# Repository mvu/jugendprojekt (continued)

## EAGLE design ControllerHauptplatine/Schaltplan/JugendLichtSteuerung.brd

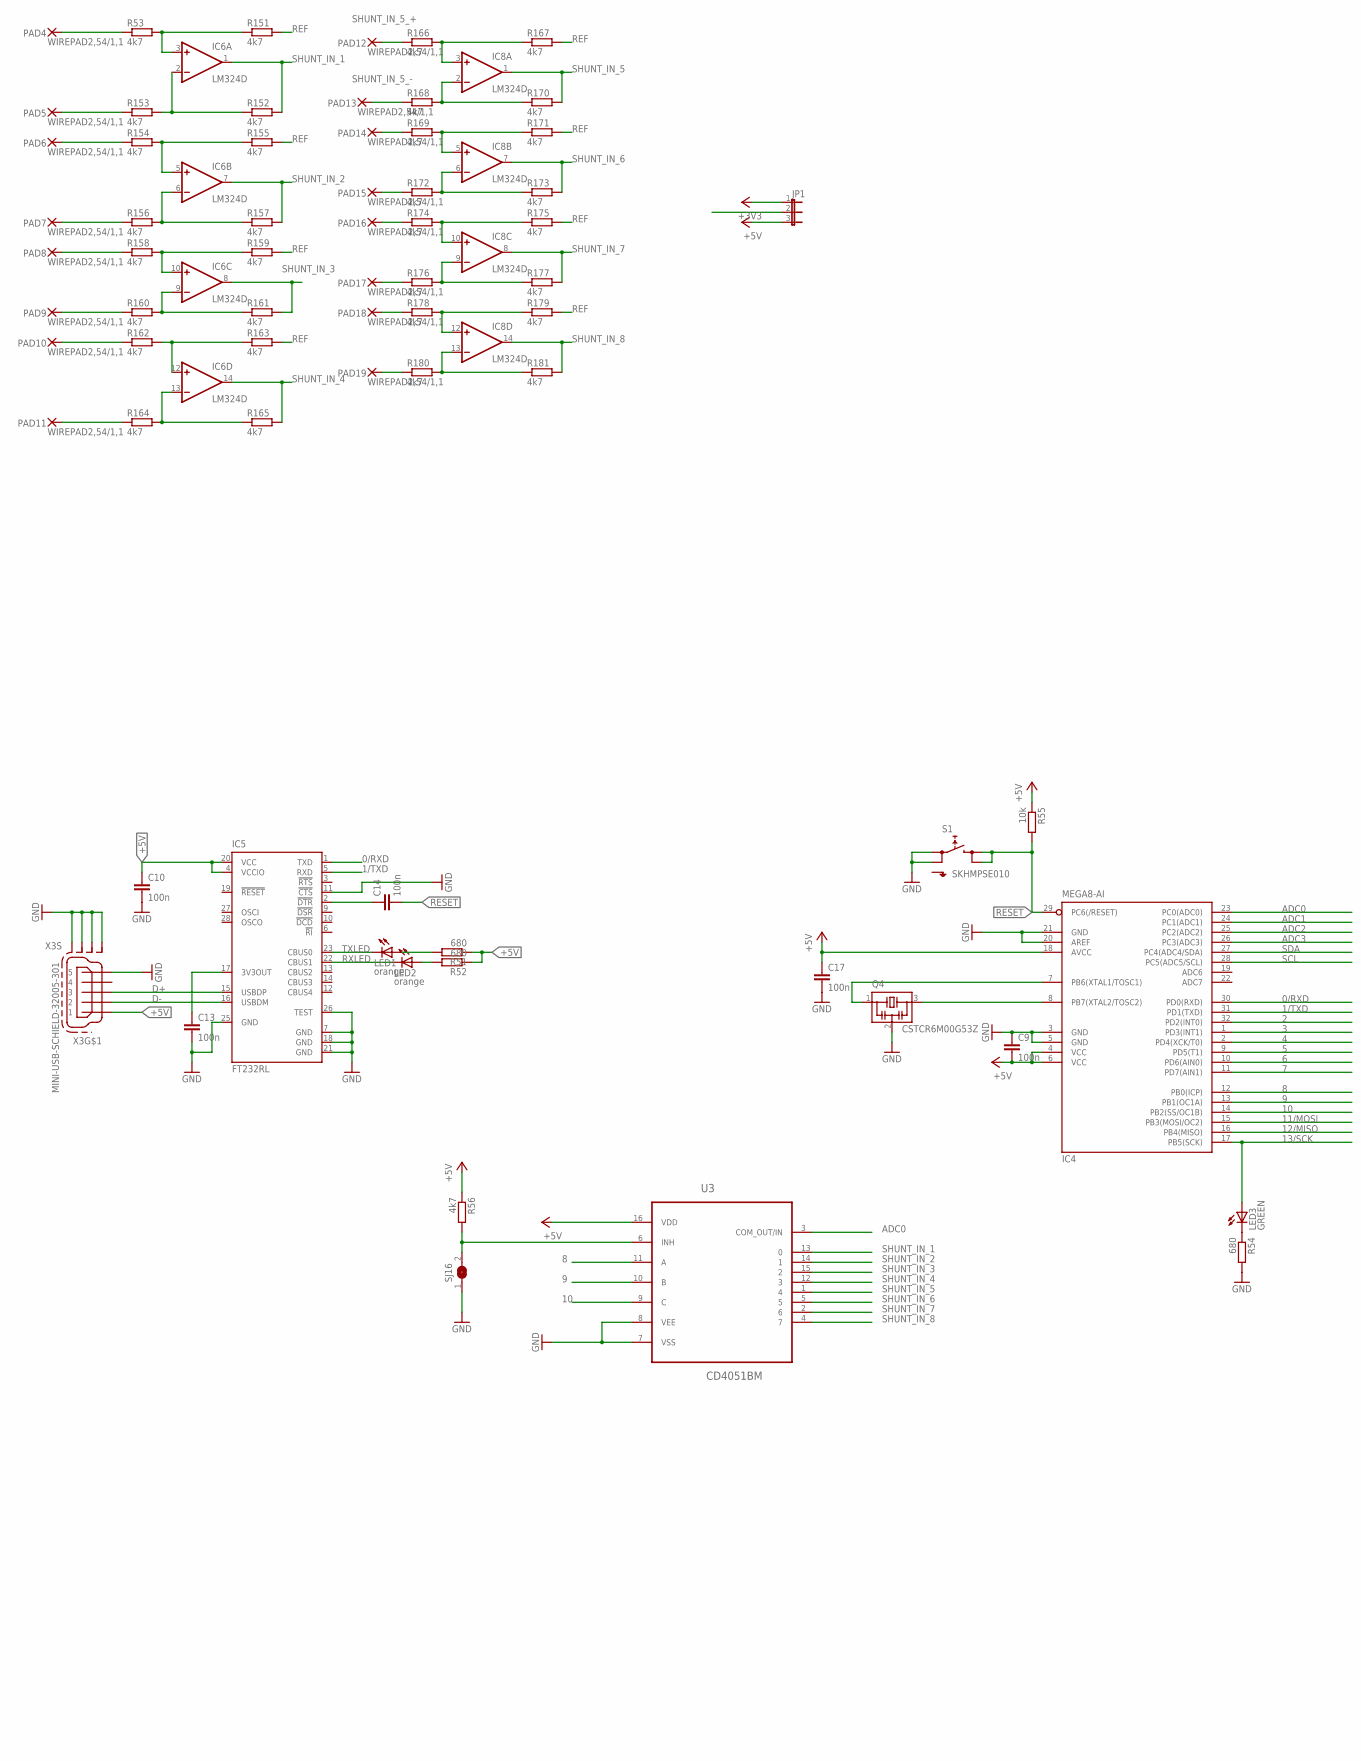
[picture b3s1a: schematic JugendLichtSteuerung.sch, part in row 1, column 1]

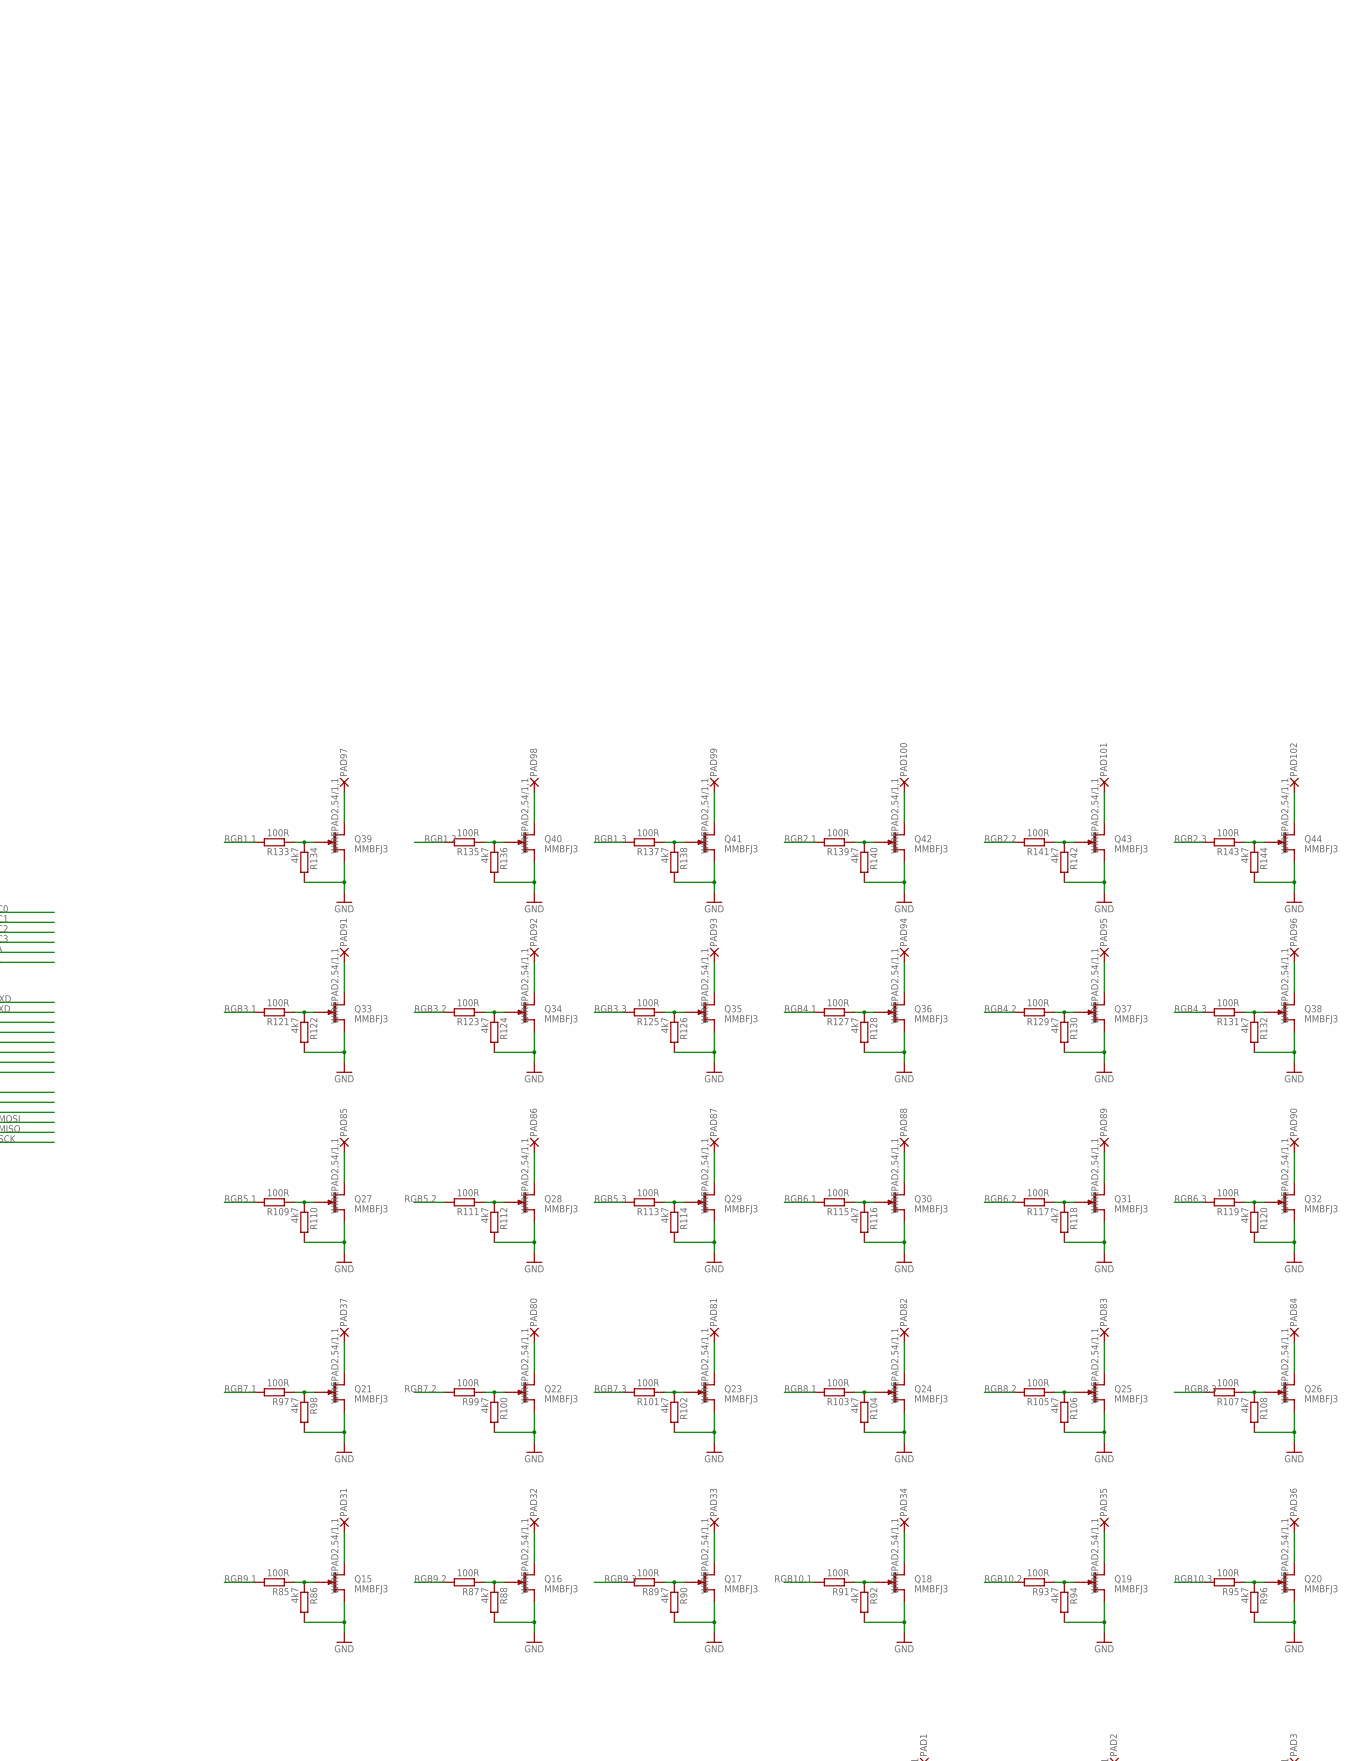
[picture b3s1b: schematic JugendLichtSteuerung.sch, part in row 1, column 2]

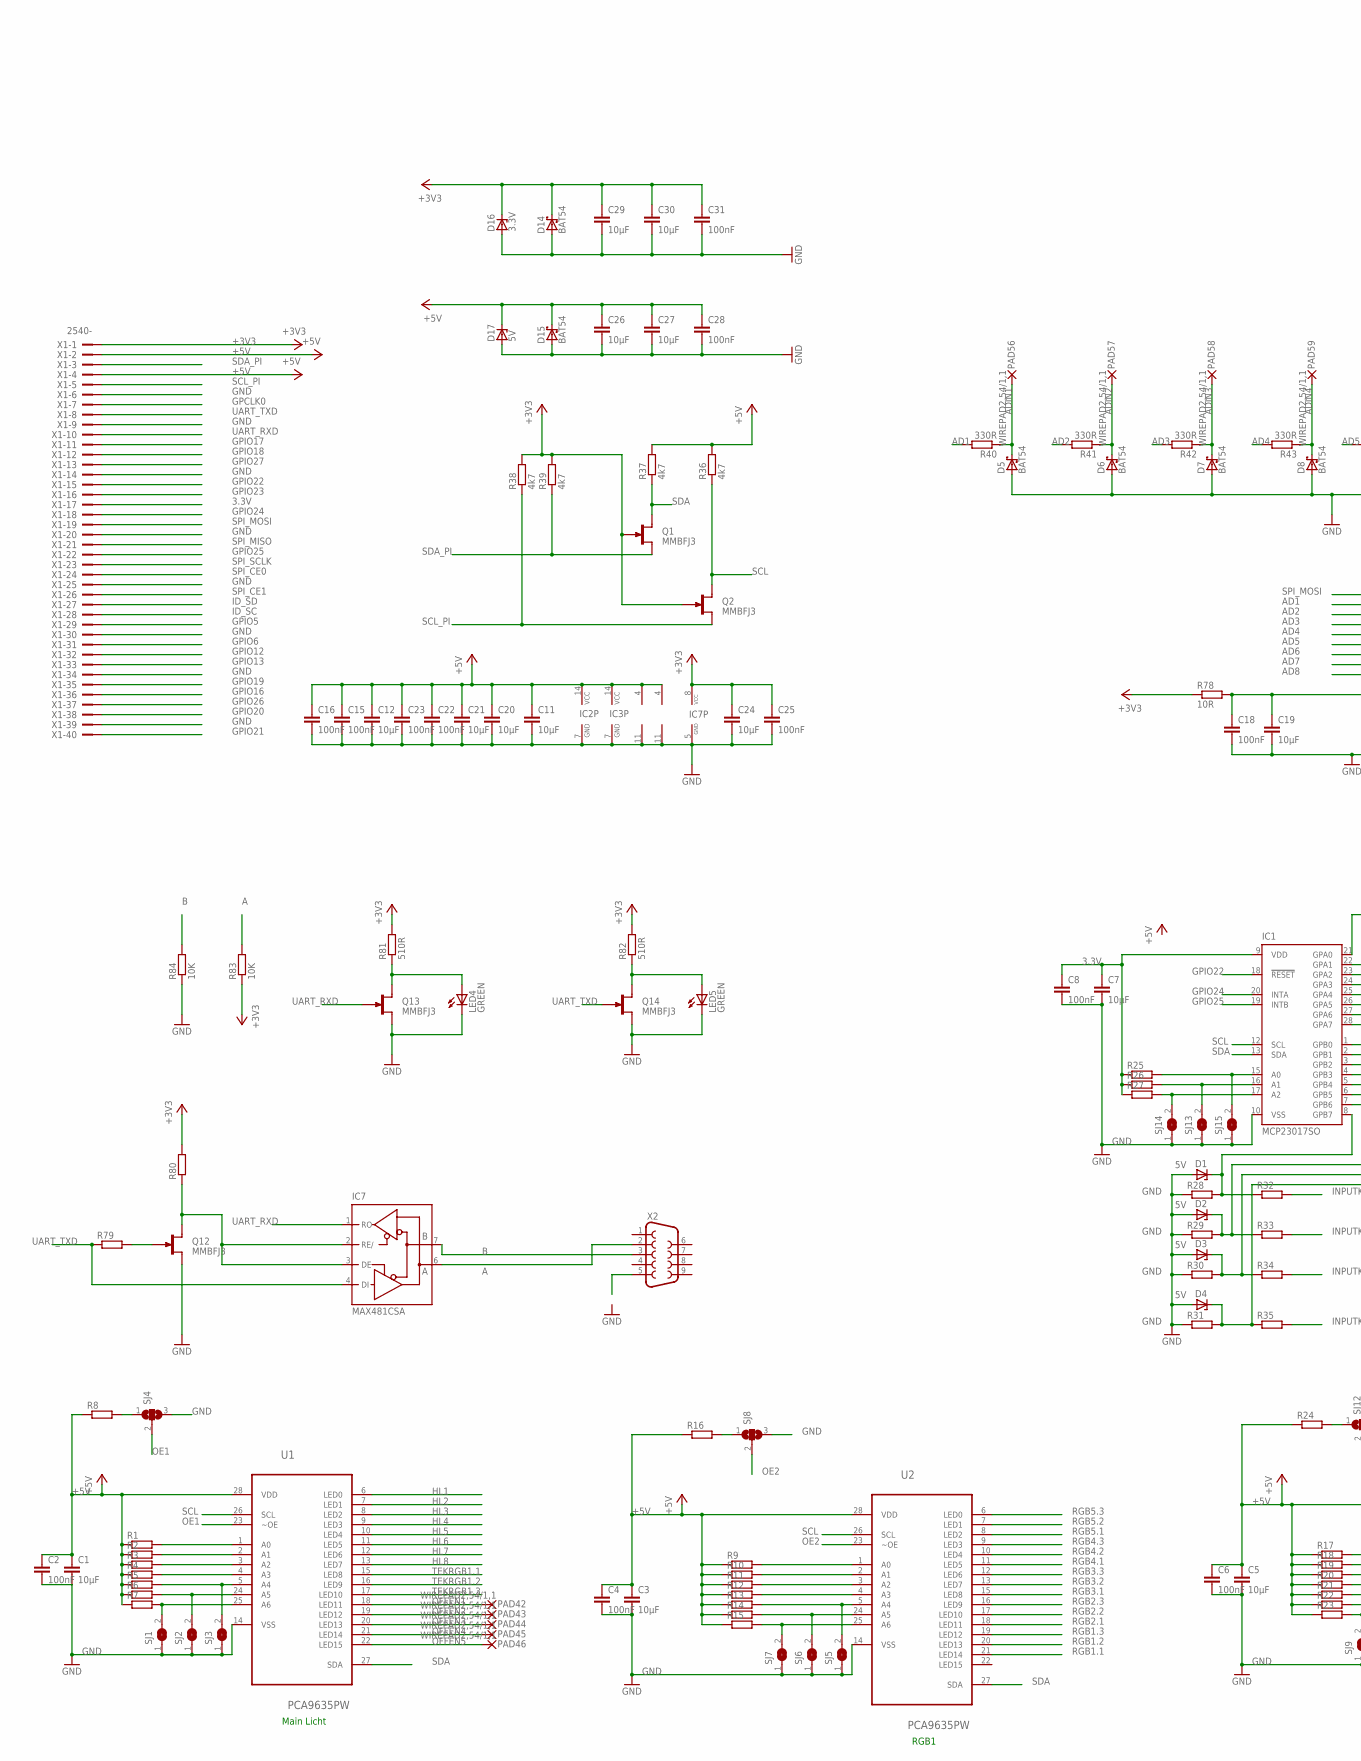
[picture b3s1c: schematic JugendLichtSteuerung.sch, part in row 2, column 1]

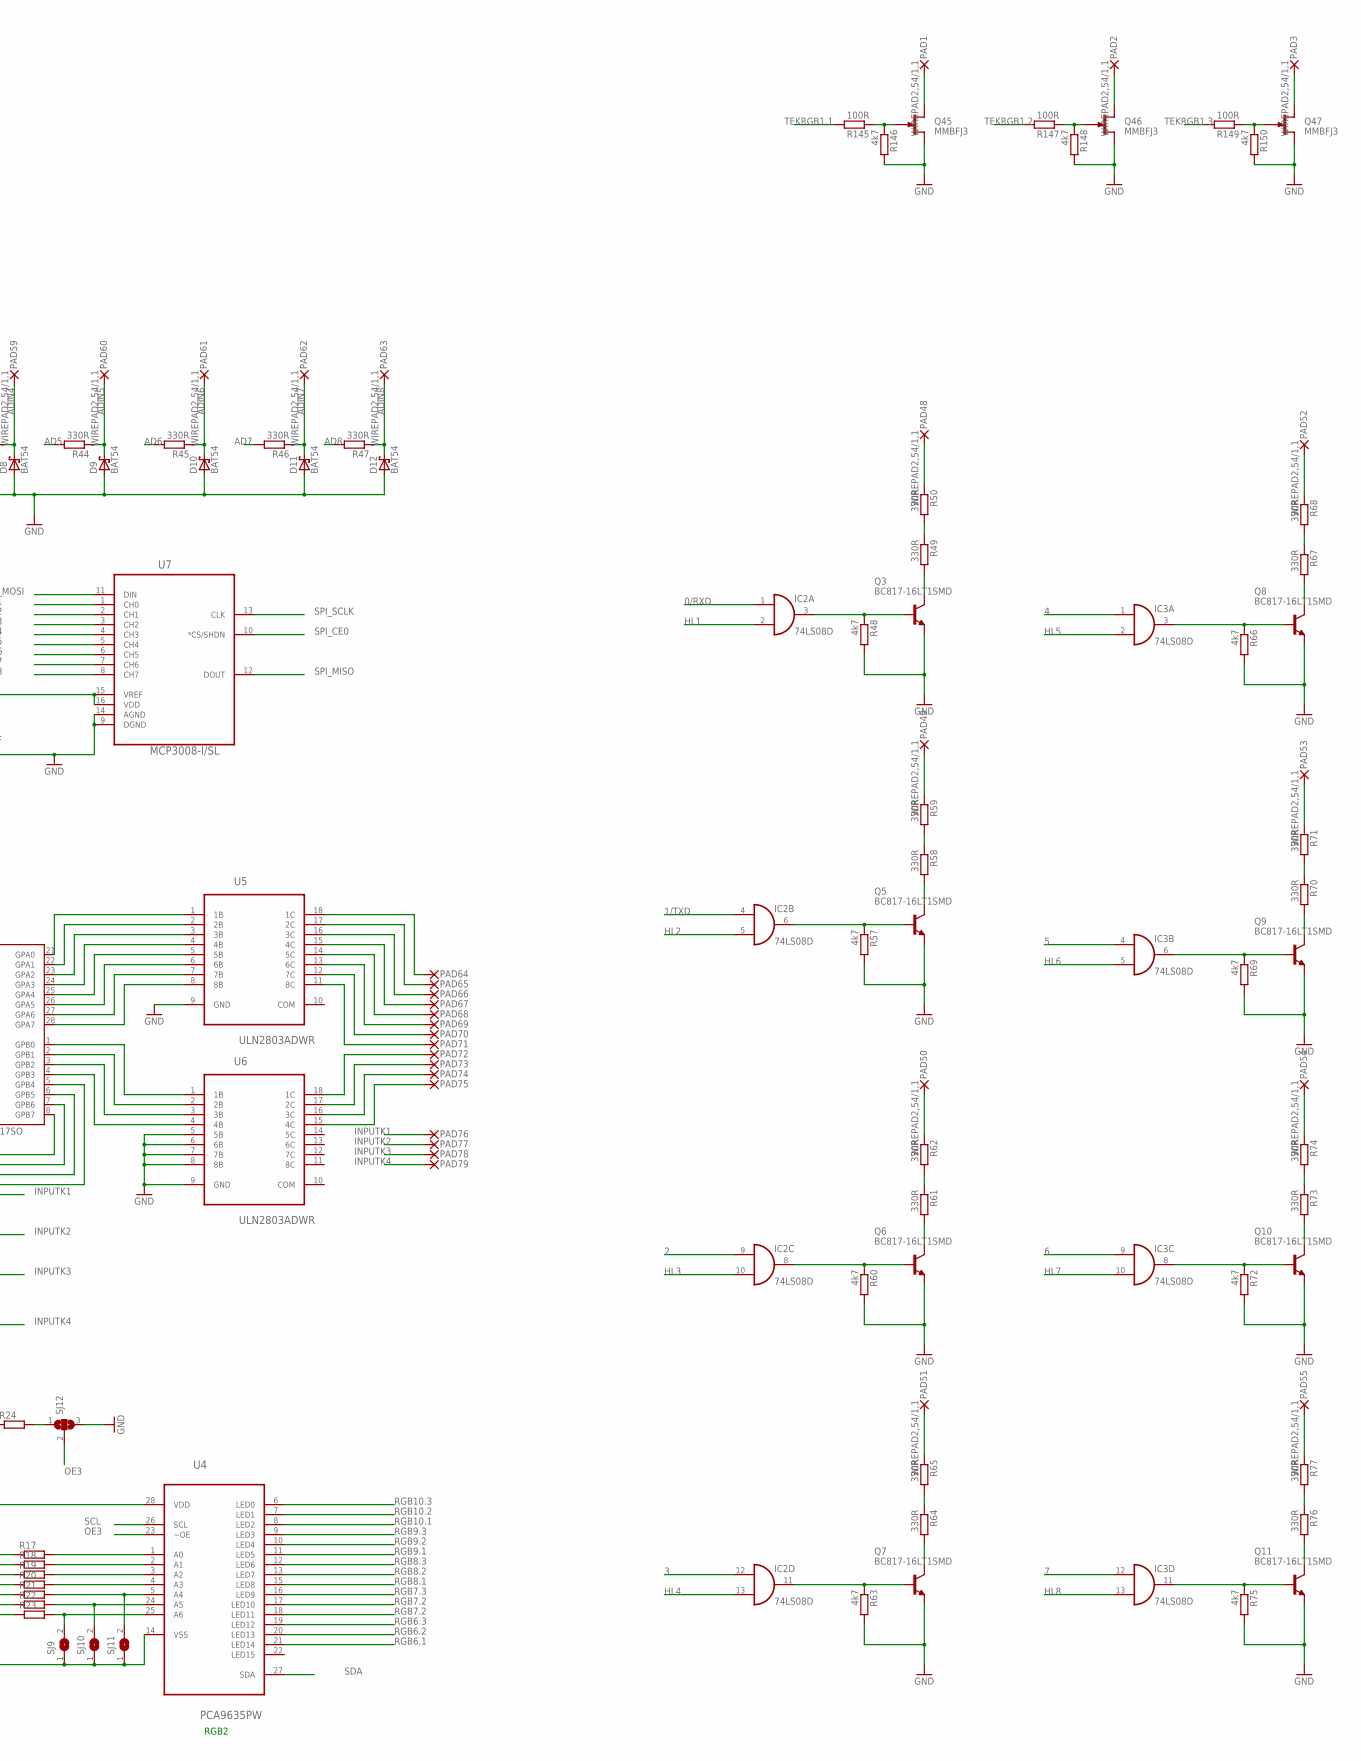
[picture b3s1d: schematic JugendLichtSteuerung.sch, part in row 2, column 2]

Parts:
C1, C3, C5, C7, C11, C12, C19, C20, C21, C24, C26, C27, C29, C30: 10µF; C0805
C2, C4, C6, C8, C15, C16, C18, C22, C23, C25, C28, C31: 100nF; C0805
C9, C10, C14: 100n; C0603
C13: 100n; C1206K
C17: 100n; C0603K
D1, D2, D3, D4, D17: 5V; SOD80C
D5, D6, D7, D8, D9, D10, D11, D12, D14, D15: BAT54; SOT23
D16: 3.3V; SOD80C
IC1: MCP23017SO; SO28W
IC2, IC3: 74LS08D; SO14
IC4: MEGA8-AI; TQFP32-08
IC5: FT232RL; SSOP28
IC6, IC8: LM324D; SO14
IC7: MAX481CSA; SO08
JP1: JP2E; JP2
LED1, LED2: orange; CHIPLED_1206
LED3, LED4, LED5: GREEN; CHIPLED_1206
PAD1, PAD2, PAD3, PAD4, PAD5, PAD6, PAD7, PAD8, PAD9, PAD10, PAD11, PAD12, PAD13, PAD14, PAD15, PAD16, PAD17, PAD18, PAD19, PAD31, PAD32, PAD33, PAD34, PAD35, PAD36, PAD37, PAD42, PAD43, PAD44, PAD45, PAD46, PAD48, PAD49, PAD50, PAD51, PAD52, PAD53, PAD54, PAD55, PAD56, PAD57, PAD58, PAD59, PAD60, PAD61, PAD62, PAD63, PAD80, PAD81, PAD82, PAD83, PAD84, PAD85, PAD86, PAD87, PAD88, PAD89, PAD90, PAD91, PAD92, PAD93, PAD94, PAD95, PAD96, PAD97, PAD98, PAD99, PAD100, PAD101, PAD102: WIREPAD2,54/1,1; 2,54/1,1
PAD64, PAD65, PAD66, PAD67, PAD68, PAD69, PAD70, PAD71, PAD72, PAD73, PAD74, PAD75, PAD76, PAD77, PAD78, PAD79: 3,81/1,4
Q1, Q2, Q12, Q13, Q14, Q15, Q16, Q17, Q18, Q19, Q20, Q21, Q22, Q23, Q24, Q25, Q26, Q27, Q28, Q29, Q30, Q31, Q32, Q33, Q34, Q35, Q36, Q37, Q38, Q39, Q40, Q41, Q42, Q43, Q44, Q45, Q46, Q47: MMBFJ3; SOT23
Q3, Q5, Q6, Q7, Q8, Q9, Q10, Q11: BC817-16LT1SMD; SOT23-BEC
Q4: CSTCR6M00G53Z; CSTCR6M
R1, R2, R3, R4, R5, R6, R7, R8, R9, R10, R11, R12, R13, R14, R15, R16, R17, R18, R19, R20, R21, R22, R23, R24, R25, R26, R27, R28, R29, R30, R31, R32, R33, R34, R35, R79, R80: R-EU_R0603; R0603
R36, R37, R38, R39, R48, R53, R56, R57, R60, R63, R66, R69, R72, R75, R86, R88, R90, R92, R94, R96, R98, R100, R102, R104, R106, R108, R110, R112, R114, R116, R118, R120, R122, R124, R126, R128, R130, R132, R134, R136, R138, R140, R142, R144, R146, R148, R150, R151, R152, R153, R154, R155, R156, R157, R158, R159, R160, R161, R162, R164, R165, R166, R167, R168, R169, R170, R171, R172, R173, R174, R175, R176, R177, R178, R179, R180, R181: 4k7; R0603
R40, R41, R42, R43, R44, R45, R46, R47, R49, R50, R58, R59, R61, R62, R64, R65, R67, R68, R70, R71, R73, R74, R76, R77: 330R; R0603
R51, R52, R54: 680; R0603
R55: 10k; R0603
R78: 10R; R0603
R81, R82: 510R; R0603
R83, R84: 10K; R0603
R85, R87, R89, R91, R93, R95, R97, R99, R101, R103, R105, R107, R109, R111, R113, R115, R117, R119, R121, R123, R125, R127, R129, R131, R133, R135, R137, R139, R141, R143, R145, R147, R149: 100R; R0603
R163: 4k7; R0805
S1: SKHMPSE010; SKHMPXE010
SJ1, SJ2, SJ3, SJ5, SJ6, SJ7, SJ9, SJ10, SJ11, SJ13, SJ14, SJ15, SJ16: SJ
SJ4, SJ8, SJ12: SJ2W; SJ_2
U1, U2, U4: PCA9635PW; SOP65P640X110-28N
U3: CD4051BM; SOIC127P600X175-16N
U5, U6: ULN2803ADWR; SOIC127P1030X265-18N
U7: MCP3008-I/SL; SOIC127P600X175-16N
X1: 2540-; PAK100/2500-40
X2: F09HP
X3: MINI-USB-SCHIELD-32005-301; 32005-301

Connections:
0/RXD: IC2.1 (I0), IC4.30 (PD0(RXD)), IC5.1 (TXD)
1/TXD: IC2.4 (I0), IC4.31 (PD1(TXD)), IC5.5 (RXD)
2: IC2.9 (I0), IC4.32 (PD2(INT0))
3: IC2.12 (I0), IC4.1 (PD3(INT1))
3,3V: C13.1, IC5.17 (3V3OUT)
3.3V: C7.1, C8.1, IC1.9 (VDD), R25.1, R26.1, R27.1, X1.17
4: IC3.1 (I0), IC4.2 (PD4(XCK/T0))
5: IC3.4 (I0), IC4.9 (PD5(T1))
6: IC3.9 (I0), IC4.10 (PD6(AIN0))
7: IC3.12 (I0), IC4.11 (PD7(AIN1))
8: IC4.12 (PB0(ICP)), U3.11 (A)
9: IC4.13 (PB1(OC1A)), U3.10 (B)
10: IC4.14 (PB2(SS/OC1B)), U3.9 (C)
11/MOSI: IC4.15 (PB3(MOSI/OC2))
12/MISO: IC4.16 (PB4(MISO))
13/SCK: IC4.17 (PB5(SCK)), LED3.A
+3V3: C24.1, C25.1, C29.1, C30.1, C31.1, D14.3 (C), D16.C, IC7.8 (VCC), JP1.1, Q1.3 (G), Q2.3 (G), R38.2, R39.2, R78.1, R80.2, R81.2, R82.2, R83.1, X1.1
+5V: C1.1, C2.1, C3.1, C4.1, C5.1, C6.1, C9.2, C10.1, C11.1, C12.1, C15.1, C16.1, C17.1, C20.1, C21.1, C22.1, C23.1, C26.1, C27.1, C28.1, D15.3 (C), D17.C, IC2.14 (VCC), IC3.14 (VCC), IC4.4 (VCC), IC4.6 (VCC), IC4.18 (AVCC), IC5.4 (VCCIO), IC5.20 (VCC), IC6.4 (V+), IC8.4 (V+), JP1.3, R1.1, R2.1, R3.1, R4.1, R5.1, R6.1, R7.1, R8.1, R9.1, R10.1, R11.1, R12.1, R13.1, R14.1, R15.1, R16.1, R17.1, R18.1, R19.1, R20.1, R21.1, R22.1, R23.1, R24.1, R36.2, R37.2, R51.1, R52.1, R55.1, R56.1, U1.28 (VDD), U2.28 (VDD), U3.16 (VDD), U4.28 (VDD), X1.2, X1.4, X3.1
A: IC7.6 (A), R83.2, X2.2
AD1: R40.2, U7.1 (CH0)
AD2: R41.2, U7.2 (CH1)
AD3: R42.2, U7.3 (CH2)
AD4: R43.2, U7.4 (CH3)
AD5: R44.2, U7.5 (CH4)
AD6: R45.2, U7.6 (CH5)
AD7: R46.2, U7.7 (CH6)
AD8: R47.2, U7.8 (CH7)
ADC0: IC4.23 (PC0(ADC0)), U3.3 (COM_OUT/IN)
ADC1: IC4.24 (PC1(ADC1))
ADC2: IC4.25 (PC2(ADC2))
ADC3: IC4.26 (PC3(ADC3))
ADIN1: D5.3 (C), PAD56.1, R40.1
ADIN2: D6.3 (C), PAD57.1, R41.1
ADIN3: D7.3 (C), PAD58.1, R42.1
ADIN4: D8.3 (C), PAD59.1, R43.1
ADIN5: D9.3 (C), PAD60.1, R44.1
ADIN6: D10.3 (C), PAD61.1, R45.1
ADIN7: D11.3 (C), PAD62.1, R46.1
ADIN8: D12.3 (C), PAD63.1, R47.1
B: IC7.7 (B), R84.2, X2.3
D+: IC5.15 (USBDP), X3.3
D-: IC5.16 (USBDM), X3.2
GND: C1.2, C2.2, C3.2, C4.2, C5.2, C6.2, C7.2, C8.2, C9.1, C10.2, C11.2, C12.2, C13.2, C15.2, C16.2, C17.2, C18.2, C19.2, C20.2, C21.2, C22.2, C23.2, C24.2, C25.2, C26.2, C27.2, C28.2, C29.2, C30.2, C31.2, D1.A, D2.A, D3.A, D4.A, D5.1 (A), D6.1 (A), D7.1 (A), D8.1 (A), D9.1 (A), D10.1 (A), D11.1 (A), D12.1 (A), D14.1 (A), D15.1 (A), D16.A, D17.A, IC1.10 (VSS), IC2.7 (GND), IC3.7 (GND), IC4.3 (GND), IC4.5 (GND), IC4.20 (AREF), IC4.21 (GND), IC5.7 (GND), IC5.11 (!CTS), IC5.18 (GND), IC5.21 (GND), IC5.25 (GND), IC5.26 (TEST), IC6.11 (V-), IC7.5 (GND), IC8.11 (V-), LED4.C, LED5.C, Q3.E, Q4.2, Q5.E, Q6.E, Q7.E, Q8.E, Q9.E, Q10.E, Q11.E, Q12.2 (S), Q13.2 (S), Q14.2 (S), Q15.2 (S), Q16.2 (S), Q17.2 (S), Q18.2 (S), Q19.2 (S), Q20.2 (S), Q21.2 (S), Q22.2 (S), Q23.2 (S), Q24.2 (S), Q25.2 (S), Q26.2 (S), Q27.2 (S), Q28.2 (S), Q29.2 (S), Q30.2 (S), Q31.2 (S), Q32.2 (S), Q33.2 (S), Q34.2 (S), Q35.2 (S), Q36.2 (S), Q37.2 (S), Q38.2 (S), Q39.2 (S), Q40.2 (S), Q41.2 (S), Q42.2 (S), Q43.2 (S), Q44.2 (S), Q45.2 (S), Q46.2 (S), Q47.2 (S), R28.1, R29.1, R30.1, R31.1, R48.2, R54.2, R57.2, R60.2, R63.2, R66.2, R69.2, R72.2, R75.2, R84.1, R86.2, R88.2, R90.2, R92.2, R94.2, R96.2, R98.2, R100.2, R102.2, R104.2, R106.2, R108.2, R110.2, R112.2, R114.2, R116.2, R118.2, R120.2, R122.2, R124.2, R126.2, R128.2, R130.2, R132.2, R134.2, R136.2, R138.2, R140.2, R142.2, R144.2, R146.2, R148.2, R150.2, S1.1 (1.1), S1.2 (1.2), SJ1.1, SJ2.1, SJ3.1, SJ4.3, SJ5.1, SJ6.1, SJ7.1, SJ8.3, SJ9.1, SJ10.1, SJ11.1, SJ12.3, SJ13.1, SJ14.1, SJ15.1, SJ16.1, U1.14 (VSS), U2.14 (VSS), U3.7 (VSS), U3.8 (VEE), U4.14 (VSS), U5.9 (GND), U6.5 (5B), U6.6 (6B), U6.7 (7B), U6.8 (8B), U6.9 (GND), U7.9 (DGND), U7.14 (AGND), X1.6, X1.9, X1.14, X1.20, X1.25, X1.30, X1.34, X1.39, X3.5, X3.M1 (S1), X3.M2 (S2), X3.M3 (S3), X3.M4 (S4)
GPCLK0: X1.7
GPIO5: X1.29
GPIO6: X1.31
GPIO12: X1.32
GPIO13: X1.33
GPIO16: X1.36
GPIO17: X1.11
GPIO18: X1.12
GPIO19: X1.35
GPIO20: X1.38
GPIO21: X1.40
GPIO22: IC1.18 (!RESET), X1.15
GPIO23: X1.16
GPIO24: IC1.20 (INTA), X1.18
GPIO25: IC1.19 (INTB), X1.22
GPIO26: X1.37
GPIO27: X1.13
HL1: IC2.2 (I1), U1.6 (LED0)
HL2: IC2.5 (I1), U1.7 (LED1)
HL3: IC2.10 (I1), U1.8 (LED2)
HL4: IC2.13 (I1), U1.9 (LED3)
HL5: IC3.2 (I1), U1.10 (LED4)
HL6: IC3.5 (I1), U1.11 (LED5)
HL7: IC3.10 (I1), U1.12 (LED6)
HL8: IC3.13 (I1), U1.13 (LED7)
ID_SC: X1.28
ID_SD: X1.27
INPUT1: D1.C, IC1.8 (GPB7), R28.2, R32.1
INPUT2: D2.C, IC1.7 (GPB6), R29.2, R33.1
INPUT3: D3.C, IC1.6 (GPB5), R30.2, R34.1
INPUT4: D4.C, IC1.5 (GPB4), R31.2, R35.1
INPUTK1: PAD76.1, R32.2
INPUTK2: PAD77.1, R33.2
INPUTK3: PAD78.1, R34.2
INPUTK4: PAD79.1, R35.2
unnamed: IC1.28 (GPA7), U5.8 (8B)
unnamed: IC1.27 (GPA6), U5.7 (7B)
unnamed: IC1.26 (GPA5), U5.6 (6B)
unnamed: IC1.25 (GPA4), U5.5 (5B)
unnamed: IC1.24 (GPA3), U5.4 (4B)
unnamed: IC1.23 (GPA2), U5.3 (3B)
unnamed: IC1.22 (GPA1), U5.2 (2B)
unnamed: IC1.21 (GPA0), U5.1 (1B)
unnamed: R17.2, U4.1 (A0)
unnamed: R18.2, U4.2 (A1)
unnamed: R16.2, SJ8.1
unnamed: R19.2, U4.3 (A2)
unnamed: R1.2, U1.1 (A0)
unnamed: R2.2, U1.2 (A1)
unnamed: R3.2, U1.3 (A2)
unnamed: R4.2, U1.4 (A3)
unnamed: R7.2, SJ1.2, U1.25 (A6)
unnamed: R6.2, SJ2.2, U1.24 (A5)
unnamed: R5.2, SJ3.2, U1.5 (A4)
unnamed: R8.2, SJ4.1
unnamed: R20.2, U4.4 (A3)
unnamed: R9.2, U2.1 (A0)
unnamed: R10.2, U2.2 (A1)
unnamed: R11.2, U2.3 (A2)
unnamed: R12.2, U2.4 (A3)
unnamed: R13.2, SJ5.2, U2.5 (A4)
unnamed: R14.2, SJ6.2, U2.24 (A5)
unnamed: R15.2, SJ7.2, U2.25 (A6)
unnamed: R21.2, SJ11.2, U4.5 (A4)
unnamed: R22.2, SJ10.2, U4.24 (A5)
unnamed: R23.2, SJ9.2, U4.25 (A6)
unnamed: Q45.3 (G), R145.1, R146.1
unnamed: IC1.1 (GPB0), U6.1 (1B)
unnamed: IC1.2 (GPB1), U6.2 (2B)
unnamed: IC1.3 (GPB2), U6.3 (3B)
unnamed: R24.2, SJ12.1
unnamed: IC6.2 (-IN), R152.1, R153.2
unnamed: IC1.15 (A0), R25.2, SJ15.2
unnamed: IC1.16 (A1), R26.2, SJ13.2
unnamed: IC1.17 (A2), R27.2, SJ14.2
unnamed: IC1.4 (GPB3), U6.4 (4B)
unnamed: PAD64.1, U5.18 (1C)
unnamed: PAD65.1, U5.17 (2C)
unnamed: PAD66.1, U5.16 (3C)
unnamed: PAD67.1, U5.15 (4C)
unnamed: PAD68.1, U5.14 (5C)
unnamed: PAD69.1, U5.13 (6C)
unnamed: PAD70.1, U5.12 (7C)
unnamed: PAD71.1, U5.11 (8C)
unnamed: PAD72.1, U6.18 (1C)
unnamed: PAD73.1, U6.17 (2C)
unnamed: PAD74.1, U6.16 (3C)
unnamed: PAD75.1, U6.15 (4C)
unnamed: IC2.3 (O), Q3.B, R48.1
unnamed: IC4.8 (PB7(XTAL2/TOSC2)), Q4.3
unnamed: Q3.C, R49.2
unnamed: R49.1, R50.2
unnamed: PAD48.1, R50.1
unnamed: IC4.7 (PB6(XTAL1/TOSC1)), Q4.1
unnamed: C14.1, IC5.2 (!DTR)
unnamed: LED1.A, R51.2
unnamed: LED2.A, R52.2
unnamed: LED3.C, R54.1
unnamed: R56.2, SJ16.2, U3.6 (INH)
unnamed: IC2.6 (O), Q5.B, R57.1
unnamed: Q5.C, R58.2
unnamed: R58.1, R59.2
unnamed: PAD49.1, R59.1
unnamed: IC2.8 (O), Q6.B, R60.1
unnamed: Q6.C, R61.2
unnamed: R61.1, R62.2
unnamed: PAD50.1, R62.1
unnamed: IC2.11 (O), Q7.B, R63.1
unnamed: Q7.C, R64.2
unnamed: R64.1, R65.2
unnamed: PAD51.1, R65.1
unnamed: IC3.3 (O), Q8.B, R66.1
unnamed: Q8.C, R67.2
unnamed: R67.1, R68.2
unnamed: PAD52.1, R68.1
unnamed: IC3.6 (O), Q9.B, R69.1
unnamed: Q9.C, R70.2
unnamed: R70.1, R71.2
unnamed: PAD53.1, R71.1
unnamed: IC3.8 (O), Q10.B, R72.1
unnamed: Q10.C, R73.2
unnamed: R73.1, R74.2
unnamed: PAD54.1, R74.1
unnamed: IC3.11 (O), Q11.B, R75.1
unnamed: Q11.C, R76.2
unnamed: R76.1, R77.2
unnamed: PAD55.1, R77.1
unnamed: Q15.3 (G), R85.1, R86.1
unnamed: C18.1, C19.1, R78.2, U7.15 (VREF), U7.16 (VDD)
unnamed: PAD1.1, Q45.1 (D)
unnamed: Q12.3 (G), R79.2
unnamed: PAD31.1, Q15.1 (D)
unnamed: IC7.2 (RE/), IC7.3 (DE), Q12.1 (D), R80.1
unnamed: Q16.3 (G), R87.1, R88.1
unnamed: Q46.3 (G), R147.1, R148.1
unnamed: LED4.A, Q13.1 (D), R81.1
unnamed: LED5.A, Q14.1 (D), R82.1
unnamed: PAD32.1, Q16.1 (D)
unnamed: IC6.3 (+IN), R53.2, R151.1
unnamed: Q17.3 (G), R89.1, R90.1
unnamed: PAD2.1, Q46.1 (D)
unnamed: PAD33.1, Q17.1 (D)
unnamed: Q18.3 (G), R91.1, R92.1
unnamed: Q47.3 (G), R149.1, R150.1
unnamed: PAD34.1, Q18.1 (D)
unnamed: Q19.3 (G), R93.1, R94.1
unnamed: PAD3.1, Q47.1 (D)
unnamed: PAD35.1, Q19.1 (D)
unnamed: Q20.3 (G), R95.1, R96.1
unnamed: IC6.5 (+IN), R154.2, R155.1
unnamed: PAD36.1, Q20.1 (D)
unnamed: Q21.3 (G), R97.1, R98.1
unnamed: IC6.6 (-IN), R156.2, R157.1
unnamed: PAD37.1, Q21.1 (D)
unnamed: Q22.3 (G), R99.1, R100.1
unnamed: PAD80.1, Q22.1 (D)
unnamed: Q23.3 (G), R101.1, R102.1
unnamed: IC6.10 (+IN), R158.2, R159.1
unnamed: PAD81.1, Q23.1 (D)
unnamed: Q24.3 (G), R103.1, R104.1
unnamed: IC6.9 (-IN), R160.2, R161.1
unnamed: PAD82.1, Q24.1 (D)
unnamed: Q25.3 (G), R105.1, R106.1
unnamed: PAD83.1, Q25.1 (D)
unnamed: Q26.3 (G), R107.1, R108.1
unnamed: IC6.12 (+IN), R162.2, R163.1
unnamed: PAD84.1, Q26.1 (D)
unnamed: Q27.3 (G), R109.1, R110.1
unnamed: IC6.13 (-IN), R164.2, R165.1
unnamed: PAD85.1, Q27.1 (D)
unnamed: Q28.3 (G), R111.1, R112.1
unnamed: PAD86.1, Q28.1 (D)
unnamed: Q29.3 (G), R113.1, R114.1
unnamed: IC8.3 (+IN), R166.2, R167.1
unnamed: PAD87.1, Q29.1 (D)
unnamed: Q30.3 (G), R115.1, R116.1
unnamed: IC8.2 (-IN), R168.2, R170.1
unnamed: PAD88.1, Q30.1 (D)
unnamed: Q31.3 (G), R117.1, R118.1
unnamed: PAD89.1, Q31.1 (D)
unnamed: Q32.3 (G), R119.1, R120.1
unnamed: IC8.5 (+IN), R169.2, R171.1
unnamed: PAD90.1, Q32.1 (D)
unnamed: Q33.3 (G), R121.1, R122.1
unnamed: IC8.6 (-IN), R172.2, R173.1
unnamed: PAD91.1, Q33.1 (D)
unnamed: Q34.3 (G), R123.1, R124.1
unnamed: IC8.10 (+IN), R174.2, R175.1
unnamed: PAD92.1, Q34.1 (D)
unnamed: Q35.3 (G), R125.1, R126.1
unnamed: IC8.9 (-IN), R176.2, R177.1
unnamed: PAD93.1, Q35.1 (D)
unnamed: Q36.3 (G), R127.1, R128.1
unnamed: PAD94.1, Q36.1 (D)
unnamed: Q37.3 (G), R129.1, R130.1
unnamed: IC8.12 (+IN), R178.2, R179.1
unnamed: PAD95.1, Q37.1 (D)
unnamed: Q38.3 (G), R131.1, R132.1
unnamed: IC8.13 (-IN), R180.2, R181.1
unnamed: PAD96.1, Q38.1 (D)
unnamed: Q39.3 (G), R133.1, R134.1
unnamed: PAD97.1, Q39.1 (D)
unnamed: Q40.3 (G), R135.1, R136.1
unnamed: PAD98.1, Q40.1 (D)
unnamed: Q41.3 (G), R137.1, R138.1
unnamed: PAD99.1, Q41.1 (D)
unnamed: Q42.3 (G), R139.1, R140.1
unnamed: PAD100.1, Q42.1 (D)
unnamed: Q43.3 (G), R141.1, R142.1
unnamed: PAD101.1, Q43.1 (D)
unnamed: Q44.3 (G), R143.1, R144.1
unnamed: PAD102.1, Q44.1 (D)
OE1: SJ4.2, U1.23 (~OE)
OE2: SJ8.2, U2.23 (~OE)
OE3: SJ12.2, U4.23 (~OE)
OFFEN1: PAD42.1, U1.18 (LED11)
OFFEN2: PAD43.1, U1.19 (LED12)
OFFEN3: PAD44.1, U1.20 (LED13)
OFFEN4: PAD45.1, U1.21 (LED14)
OFFEN5: PAD46.1, U1.22 (LED15)
REF: JP1.2, R151.2, R155.2, R159.2, R163.2, R167.2, R171.2, R175.2, R179.2
RESET: C14.2, IC4.29 (PC6(/RESET)), R55.2, S1.3 (2.1), S1.4 (2.2)
RGB1.1: R133.2, U2.21 (LED14)
RGB1.2: R135.2, U2.20 (LED13)
RGB1.3: R137.2, U2.19 (LED12)
RGB2.1: R139.2, U2.18 (LED11)
RGB2.2: R141.2, U2.17 (LED10)
RGB2.3: R143.2, U2.16 (LED9)
RGB3.1: R121.2, U2.15 (LED8)
RGB3.2: R123.2, U2.13 (LED7)
RGB3.3: R125.2, U2.12 (LED6)
RGB4.1: R127.2, U2.11 (LED5)
RGB4.2: R129.2, U2.10 (LED4)
RGB4.3: R131.2, U2.9 (LED3)
RGB5.1: R109.2, U2.8 (LED2)
RGB5.2: R111.2, U2.7 (LED1)
RGB5.3: R113.2, U2.6 (LED0)
RGB6.1: R115.2, U4.21 (LED14)
RGB6.2: R117.2, U4.20 (LED13)
RGB6.3: R119.2, U4.19 (LED12)
RGB7.1: R97.2, U4.18 (LED11)
RGB7.2: R99.2, U4.17 (LED10)
RGB7.3: R101.2, U4.16 (LED9)
RGB8.1: R103.2, U4.15 (LED8)
RGB8.2: R105.2, U4.13 (LED7)
RGB8.3: R107.2, U4.12 (LED6)
RGB9.1: R85.2, U4.11 (LED5)
RGB9.2: R87.2, U4.10 (LED4)
RGB9.3: R89.2, U4.9 (LED3)
RGB10.1: R91.2, U4.8 (LED2)
RGB10.2: R93.2, U4.7 (LED1)
RGB10.3: R95.2, U4.6 (LED0)
RXLED: IC5.22 (CBUS1), LED2.C
SCL: IC1.12 (SCL), IC4.28 (PC5(ADC5/SCL)), Q2.1 (D), R36.1, U1.26 (SCL), U2.26 (SCL), U4.26 (SCL)
SCL_PI: Q2.2 (S), R38.1, X1.5
SDA: IC1.13 (SDA), IC4.27 (PC4(ADC4/SDA)), Q1.1 (D), R37.1, U1.27 (SDA), U2.27 (SDA), U4.27 (SDA)
SDA_PI: Q1.2 (S), R39.1, X1.3
SHUNT_IN_1: IC6.1 (OUT), R152.2, U3.13 (0)
SHUNT_IN_1_+: PAD4.1, R53.1
SHUNT_IN_1_-: PAD5.1, R153.1
SHUNT_IN_2: IC6.7 (OUT), R157.2, U3.14 (1)
SHUNT_IN_2_+: PAD6.1, R154.1
SHUNT_IN_2_-: PAD7.1, R156.1
SHUNT_IN_3: IC6.8 (OUT), R161.2, U3.15 (2)
SHUNT_IN_3_+: PAD8.1, R158.1
SHUNT_IN_3_-: PAD9.1, R160.1
SHUNT_IN_4: IC6.14 (OUT), R165.2, U3.12 (3)
SHUNT_IN_4+: PAD10.1, R162.1
SHUNT_IN_4_-: PAD11.1, R164.1
SHUNT_IN_5: IC8.1 (OUT), R170.2, U3.1 (4)
SHUNT_IN_5_+: PAD12.1, R166.1
SHUNT_IN_5_-: PAD13.1, R168.1
SHUNT_IN_6: IC8.7 (OUT), R173.2, U3.5
SHUNT_IN_6_+: PAD14.1, R169.1
SHUNT_IN_6_-: PAD15.1, R172.1
SHUNT_IN_7: IC8.8 (OUT), R177.2, U3.2 (6)
SHUNT_IN_7_+: PAD16.1, R174.1
SHUNT_IN_7_-: PAD17.1, R176.1
SHUNT_IN_8: IC8.14 (OUT), R181.2, U3.4 (7)
SHUNT_IN_8_+: PAD18.1, R178.1
SHUNT_IN_8_-: PAD19.1, R180.1
SPI_CE0: U7.10 (*CS/SHDN), X1.24
SPI_CE1: X1.26
SPI_MISO: U7.12 (DOUT), X1.21
SPI_MOSI: U7.11 (DIN), X1.19
SPI_SCLK: U7.13 (CLK), X1.23
TEKRGB1.1: R145.2, U1.15 (LED8)
TEKRGB1.2: R147.2, U1.16 (LED9)
TEKRGB1.3: R149.2, U1.17 (LED10)
TXLED: IC5.23 (CBUS0), LED1.C
UART_RXD: IC7.1 (RO), Q13.3 (G), X1.10
UART_TXD: IC7.4 (DI), Q14.3 (G), R79.1, X1.8

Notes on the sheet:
Main Licht
RGB1
RGB2

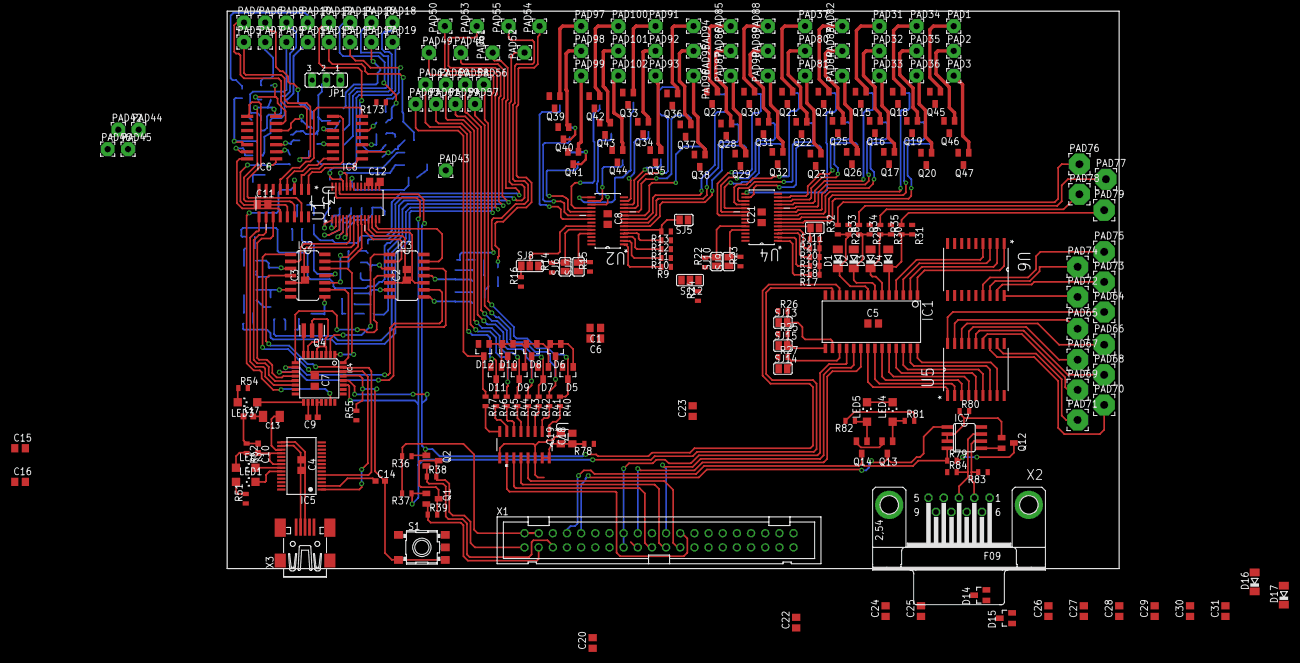
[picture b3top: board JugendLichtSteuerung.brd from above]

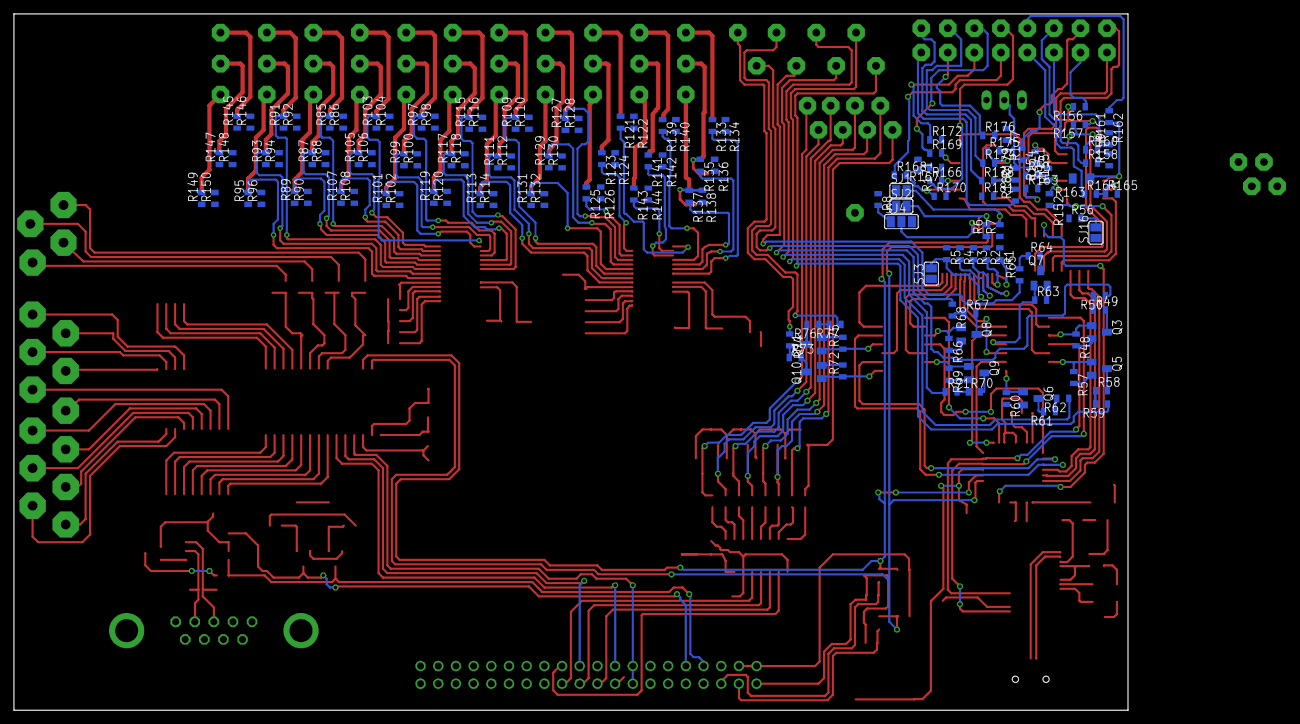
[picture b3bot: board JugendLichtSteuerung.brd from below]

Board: 2 copper layers, 160.0 x 100.0 mm, 402 parts (143 on the bottom side), 313 nets.
